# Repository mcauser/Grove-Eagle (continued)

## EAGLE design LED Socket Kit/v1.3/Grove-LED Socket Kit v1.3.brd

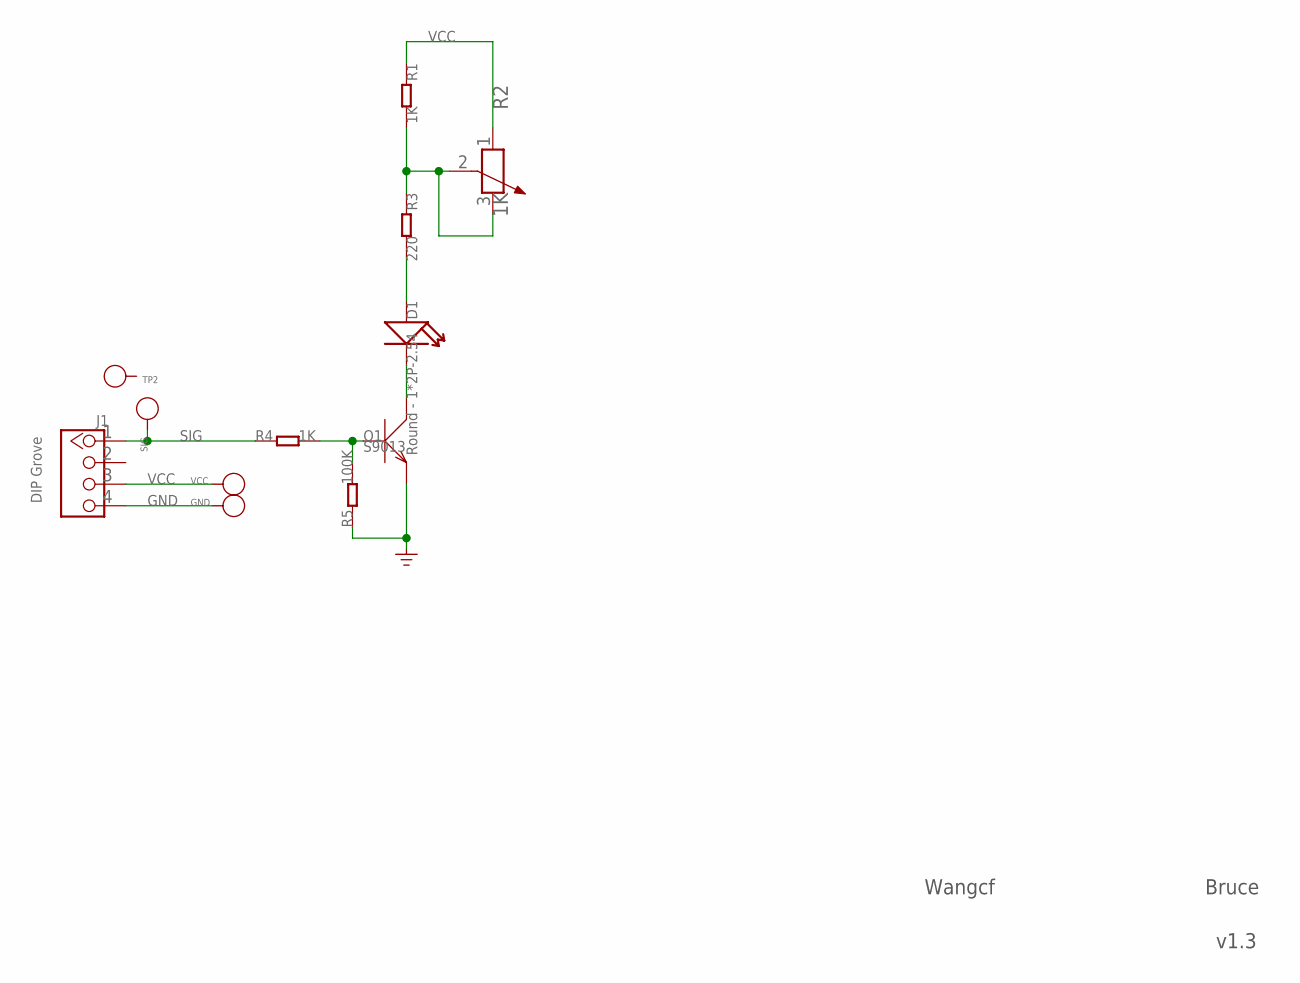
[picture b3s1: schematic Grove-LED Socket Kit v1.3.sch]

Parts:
D1: Round - 1*2P-2.54; LED-2P-2.54-6MM
GND: PAD-TEST-POINT'4545'; TP_4545
J1: DIP Grove; 2.0_1X4
Q1: S9013; SOT23
R1, R4: 1K; 0603
R2: 1K; 3P-SQUA-6.7X6.4
R3: 220; 0603
R5: 100K; 0603
SIG: PAD-TEST-POINT'4545'; TP_4545
TP2: PAD-TEST-POINT'4545'; TP_4545
VCC: PAD-TEST-POINT'4545'; TP_4545

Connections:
GND: GND.T, J1.4, Q1.2 (E), R5.1
unnamed: R1.2, R2.2 (3), R2.3 (2), R3.1
unnamed: D1.-, Q1.3 (C)
unnamed: D1.+, R3.2
unnamed: Q1.1 (B), R4.2, R5.2
SIG: J1.1, R4.1, SIG.T
VCC: J1.3, R1.1, R2.1, VCC.T

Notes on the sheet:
Wangcf
v1.3
Bruce

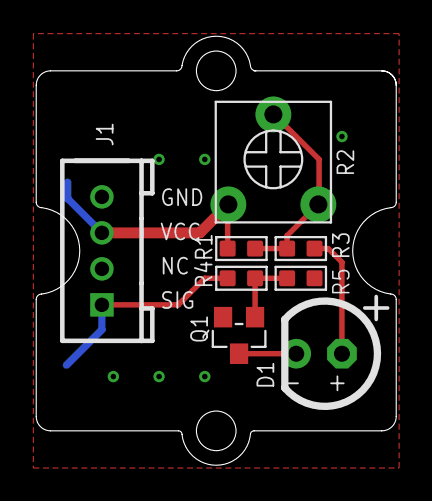
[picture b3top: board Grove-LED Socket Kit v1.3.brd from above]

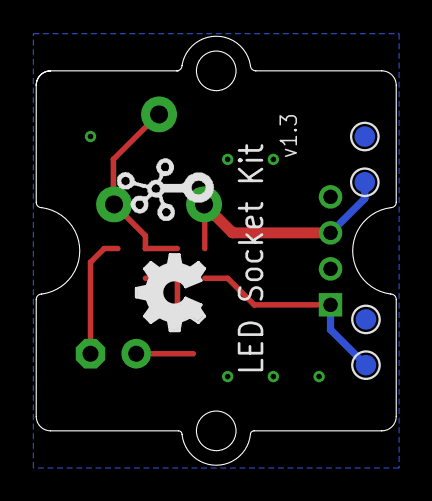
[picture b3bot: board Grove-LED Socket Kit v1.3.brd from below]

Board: 2 copper layers, 20.0 x 23.8 mm, 15 parts (6 on the bottom side), 7 nets.

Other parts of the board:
U$2: 1U-DIM-W/-DRILL
U$5: TWIGLOGO_SMALL
U$6: OSHW_FILLX150_NOTEXT

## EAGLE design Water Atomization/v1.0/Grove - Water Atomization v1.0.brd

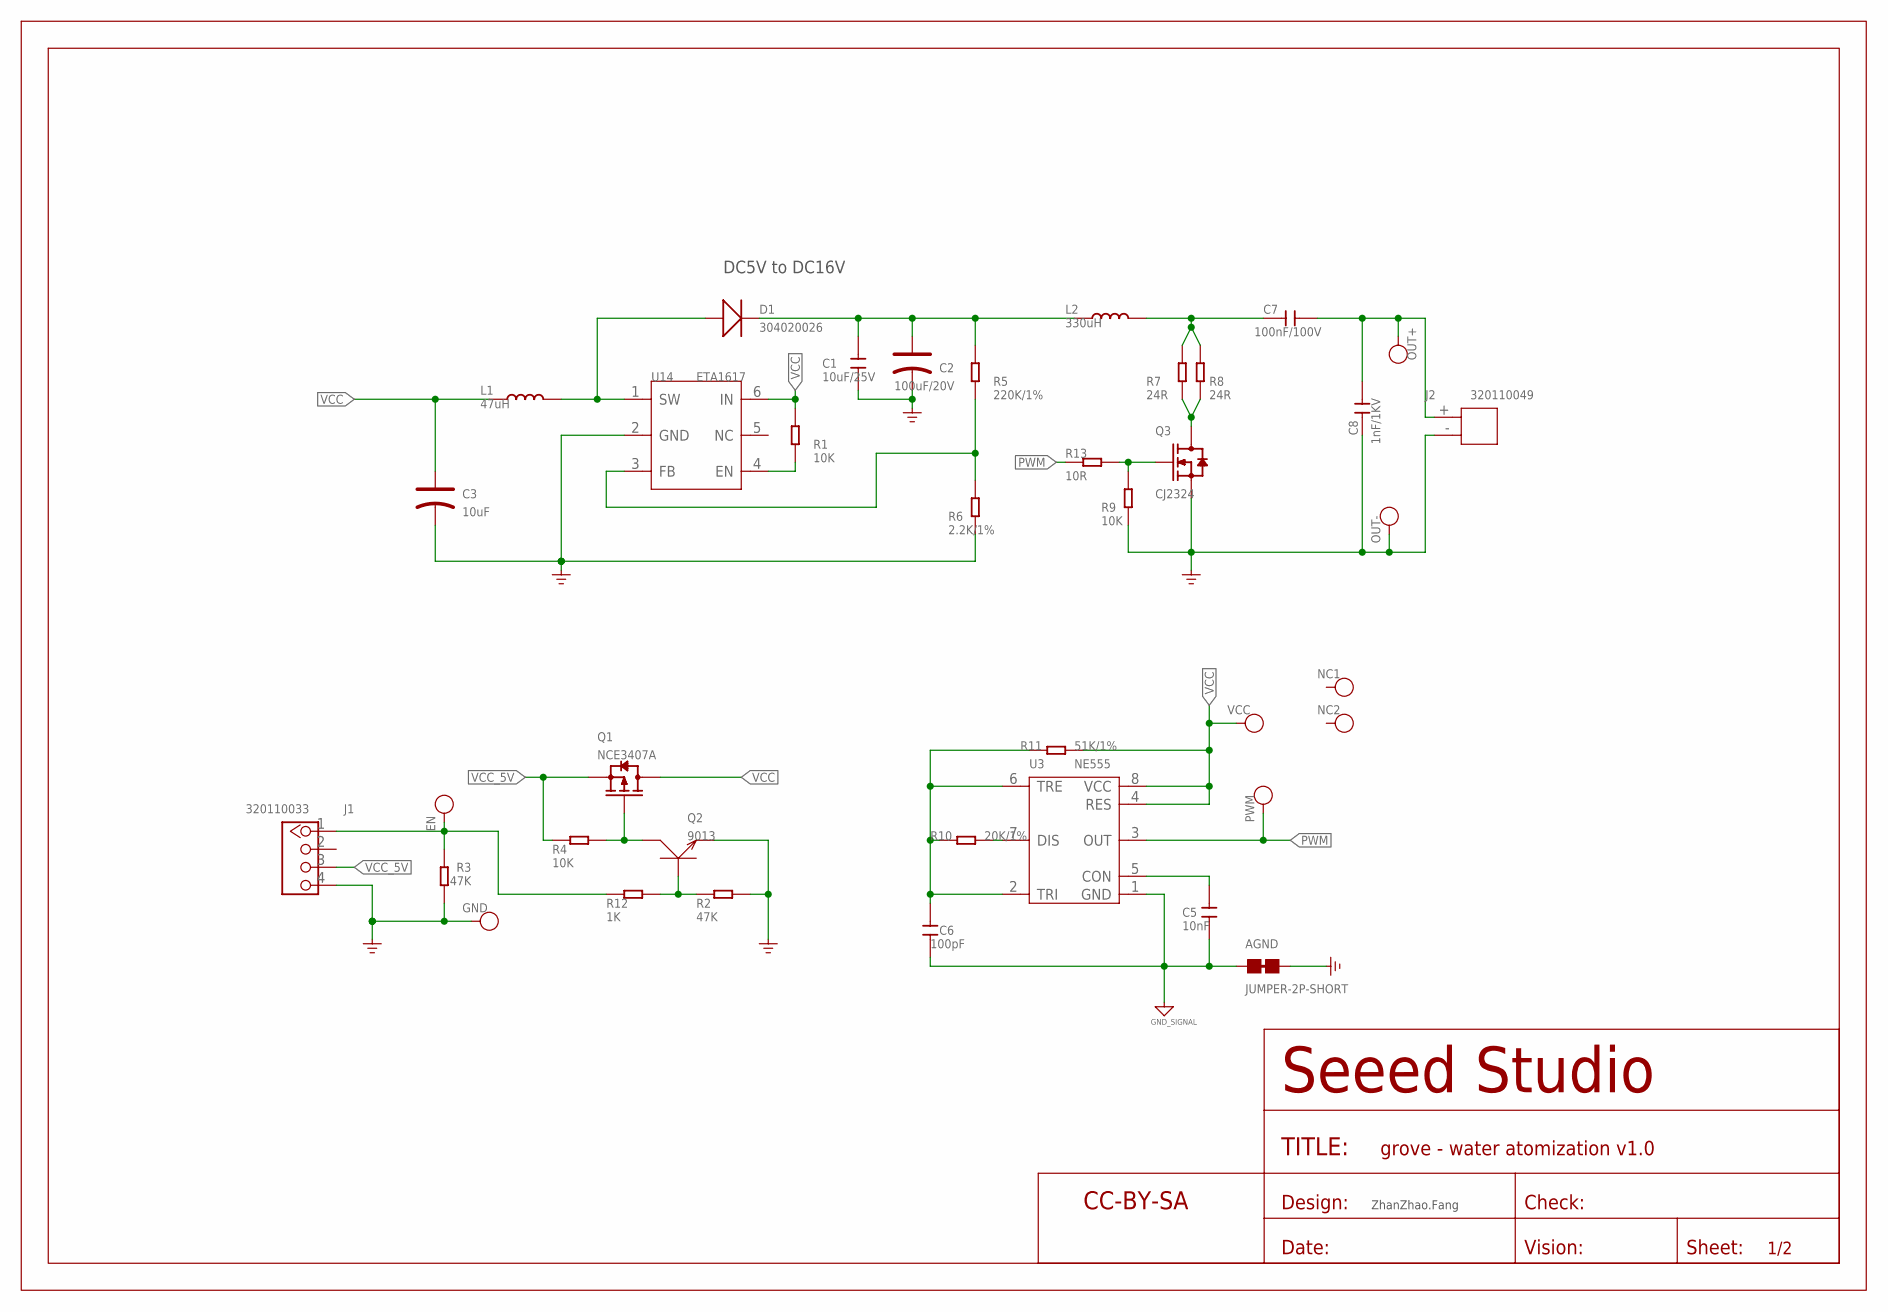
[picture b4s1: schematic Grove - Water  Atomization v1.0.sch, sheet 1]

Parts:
AGND: JUMPER-2P-SHORT; 2P-SMD-SHORT
C1: 10uF/25V; C1206
C2: 100uF/20V; AVX-D
C3: 10uF; AVX-B
C5: 10nF; C0402
C6: 100pF; C0402
C7: 100nF/100V; C0805
C8: 1nF/1KV; C1206
D1: 304020026; SOD-323
EN: DNP; TP-D45MIL
GND: DNP; TP-D45MIL
J1: 320110033; HW4-2.0
J2: 320110049; H2-2.0-6X4.5MM
L1: 47uH; INT2-SMD-4.8X4.8X3MM
L2: 330uH; INT2-SMD-4.8X4.8X3MM
NC1, NC2: DNP; TP-D45MIL
OUT+: DNP; TP-D45MIL
OUT-: DNP; TP-D45MIL
PWM: DNP; TP-D45MIL
Q1: NCE3407A; SOT-23
Q2: 9013; SOT-323
Q3: CJ2324; SOT-23
R1, R4, R9: 10K; R0402
R2, R3: 47K; R0402
R5: 220K/1%; R0402
R6: 2.2K/1%; R0402
R7, R8: 24R; R0805
R10: 20K/1%; R0402
R11: 51K/1%; R0402
R12: 1K; R0402
R13: 10R; R0402
U3: NE555; SOIC8-1.27-5X4MM
U14: ETA1617; SOT-23-6
U$1: DNP; SEEEDSTUDIO-PCB-FRAME
VCC: DNP; TP-D45MIL

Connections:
EN: EN.T, J1.1, R3.1, R12.2
FB: R5.1, R6.2, U14.3 (FB)
GND: AGND.2, C1.2, C2.-, C3.-, C8.2, GND.T, J1.4, J2.-, OUT-.T, Q2.2 (E), Q3.2 (S), R2.1, R3.2, R6.1, R9.1, U14.2 (GND)
unnamed: Q3.3 (D), R7.1, R8.1
unnamed: D1.+, L1.2, U14.1 (SW)
unnamed: R1.1, U14.4 (EN)
unnamed: C1.1, C2.+, D1.-, L2.1, R5.2
unnamed: Q1.1 (G), Q2.3 (C), R4.1
unnamed: Q2.1 (B), R2.2, R12.1
unnamed: C5.2, U3.5 (CON)
unnamed: Q3.1 (G), R9.2, R13.1
unnamed: C7.2, L2.2, R7.2, R8.2
unnamed: C7.1, C8.1, J2.+, OUT+.T
unnamed: R10.1, U3.7 (DIS)
unnamed: C6.2, R10.2, R11.1, U3.2 (TRI), U3.6 (TRE)
PWM: PWM.T, R13.2, U3.3 (OUT)
VCC: C3.+, L1.1, Q1.3 (D), R1.2, R11.2, U3.4 (RES), U3.8 (VCC), U14.6 (IN), VCC.T
VCC_5V: J1.3, Q1.2 (S), R4.2
\GND: AGND.1, C5.1, C6.1, U3.1 (GND)

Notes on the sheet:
DC5V to DC16V
ZhanZhao.Fang

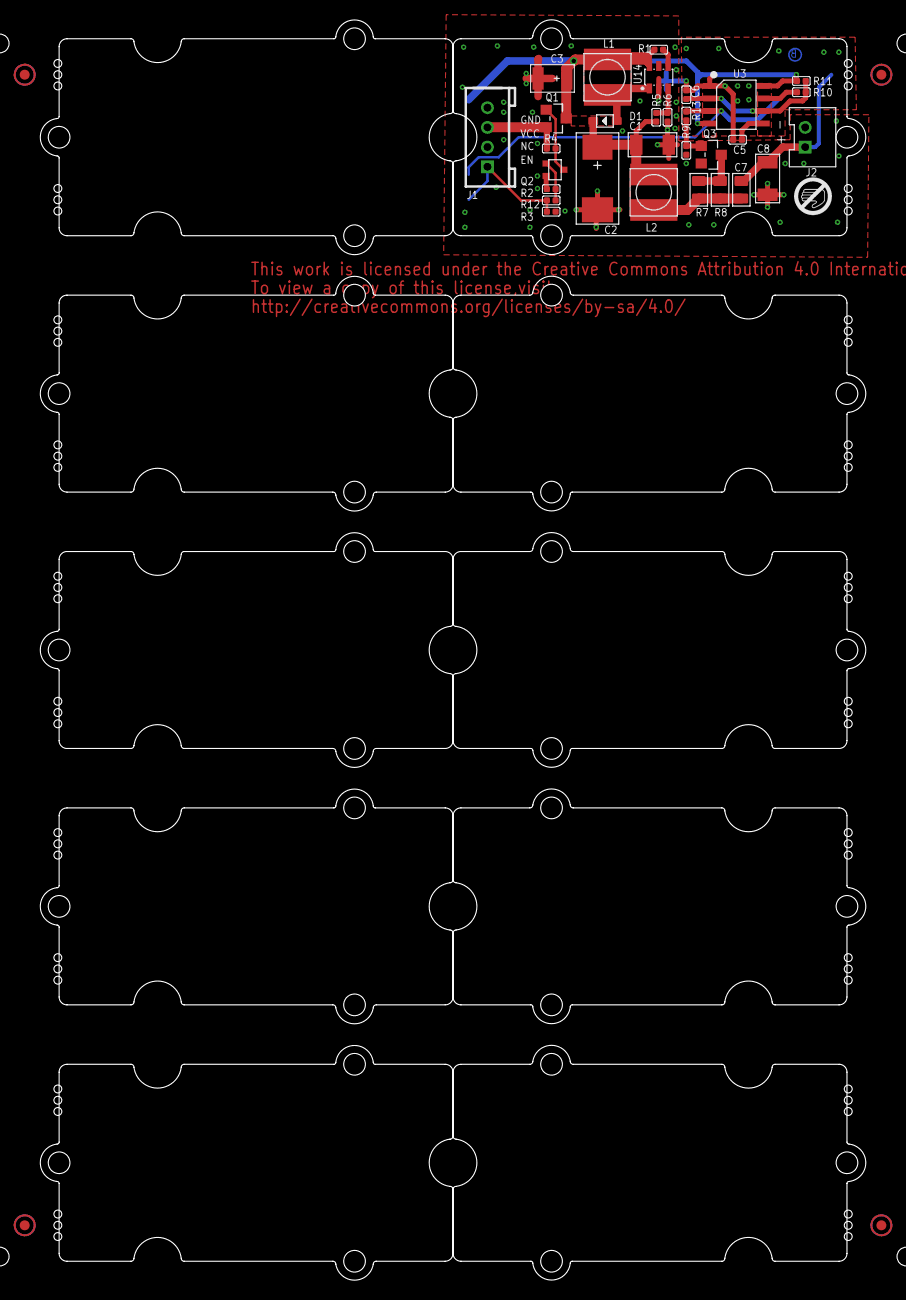
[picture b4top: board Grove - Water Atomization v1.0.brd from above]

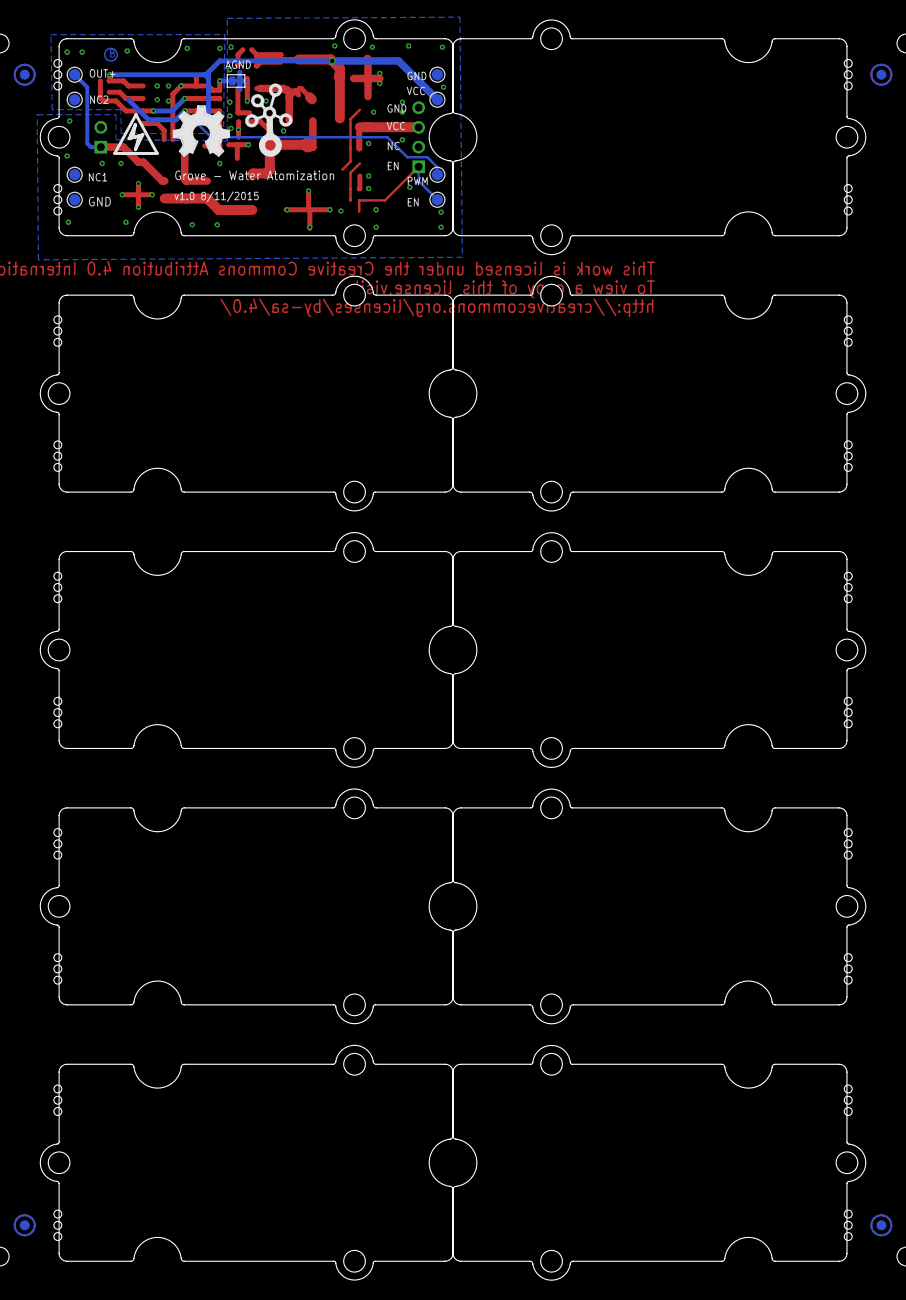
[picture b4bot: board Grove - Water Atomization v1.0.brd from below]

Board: 2 copper layers, 83.8 x 128.0 mm, 60 parts (15 on the bottom side), 19 nets.

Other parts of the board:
P1, P2, P3, P4, P5, P6, P7, P8: ROUND-MARK-1.0
U4, U5, U6, U7, U8, U9, U10, U11, U12, U13: GROVE-TEST-PLATFORM
U$5: OSHW_FILLX200_NOTEXT
U$7: GROVE-SILK-BIG

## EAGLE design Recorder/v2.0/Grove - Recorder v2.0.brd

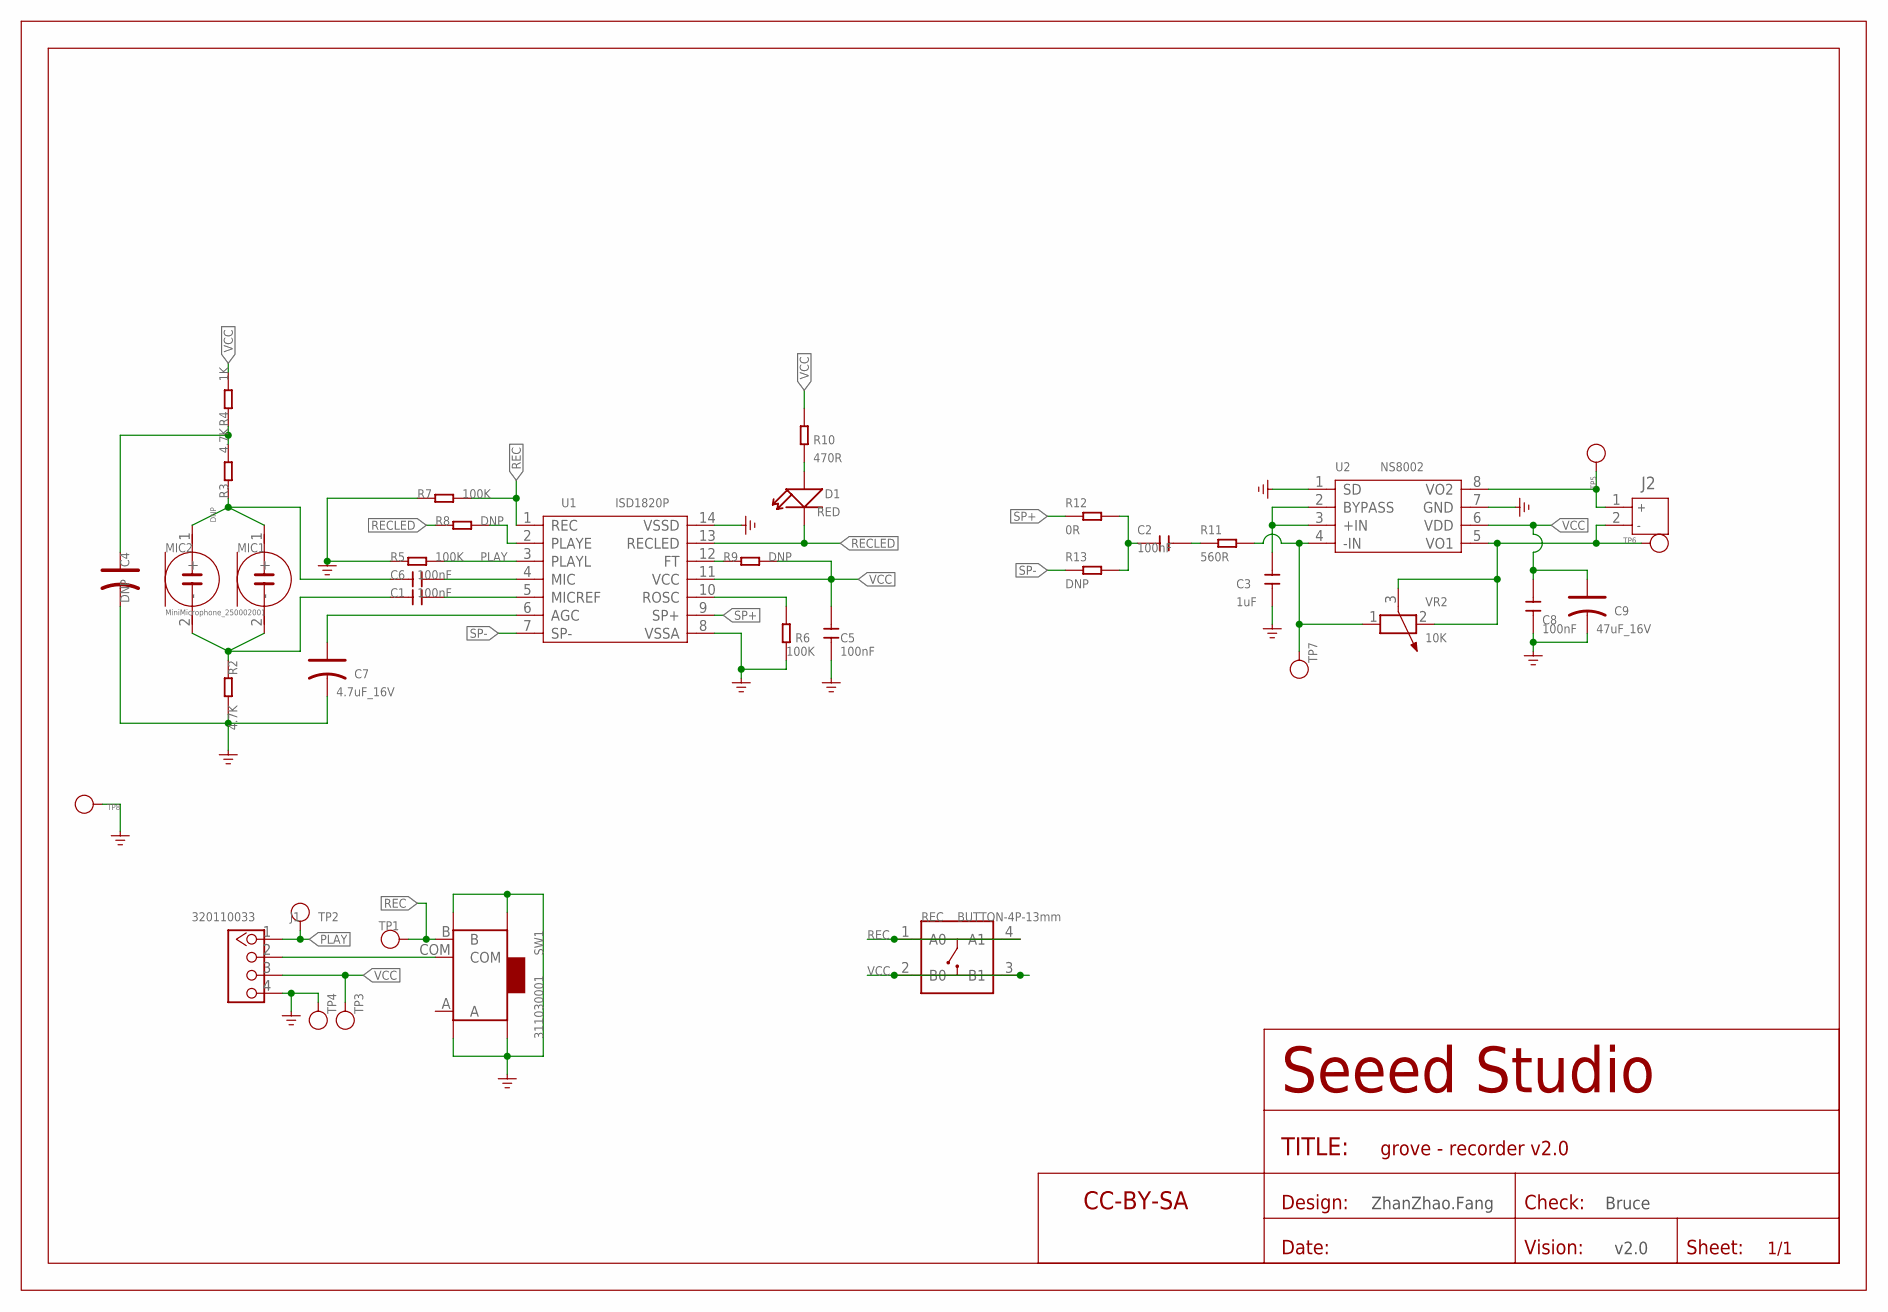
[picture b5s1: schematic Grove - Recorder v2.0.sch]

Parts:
C1, C5, C6, C8: 100nF; C0402
C2: 100nF; C0603
C3: 1uF; C0402
C4: DNP; AVX-A
C7: 4.7uF_16V; AVX-A
C9: 47uF_16V; AVX-B
D1: RED; LED-SIDE-VIEW-0603-RIGHT
FR1: SEEEDSTUDIO-OPEN-SCH-FRAME; SEEEDSTUDIO-PCB-FRAME
J1: 320110033; HW4-2.0
J2: 2P-2.0; JST-2.0
MIC1: MiniMicrophone_250002001; 2P-D8.9MM
MIC2: DNP; 2P-D8.9MM
R2, R3: 4.7K; R0402
R4: 1K; R0402
R5, R6, R7: 100K; R0402
R8, R9, R13: DNP; R0402
R10: 470R; R0402
R11: 560R; R0402
R12: 0R; R0402
REC: BUTTON-4P-13mm; 4P-6.0X6.0X5.0H
SW1: 311030001; SW7-SMD-L6.7X2.7X3.2MM
TP1, TP2, TP3, TP4, TP7: DNP; TP-D45MIL
TP5, TP6, TP8: DNP; TP_4545
U1: ISD1820P; DIP14
U2: NS8002; SOIC8-1.27-5X4MM
VR2: 10K; ADJR3-7.0X7.0X5.0MM

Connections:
GND: C3.1, C4.-, C5.2, C7.- (2), C8.1, C9.- (2), J1.4, R2.2, R5.1, R6.1, R7.1, SW1.SS1, SW1.SS2, SW1.SS3, SW1.SS4, TP4.T, TP8.T, U1.8 (VSSA), U1.14 (VSSD), U2.1 (SD), U2.7 (GND)
unnamed: R8.2, U1.2 (PLAYE)
unnamed: D1.1 (+), R10.1
unnamed: J2.1, TP5.T, U2.8 (VO2)
unnamed: J2.2, TP6.T, U2.5 (VO1), VR2.2, VR2.3
unnamed: C7.+ (1), U1.6 (AGC)
unnamed: C1.2, U1.5 (MICREF)
unnamed: C6.2, U1.4 (MIC)
unnamed: C3.2, U2.2 (BYPASS), U2.3 (+IN)
unnamed: C2.1, R11.1
unnamed: R11.2, TP7.T, U2.4 (-IN), VR2.1
unnamed: R9.1, U1.12 (FT)
unnamed: C2.2, R12.1, R13.1
unnamed: R6.2, U1.10 (ROSC)
unnamed: C4.+, R3.2, R4.1
unnamed: J1.2, SW1.COM
unnamed: C6.1, MIC1.1 (+), MIC2.1 (+), R3.1
unnamed: C1.1, MIC1.2 (-), MIC2.2 (-), R2.1
PLAY: J1.1, R5.2, TP2.T, U1.3 (PLAYL)
REC: R7.2, REC.1 (A0), REC.4 (A1), SW1.B, TP1.T, U1.1 (REC)
RECLED: D1.2 (-), R8.1, U1.13 (RECLED)
SP+: R12.2, U1.9 (SP+)
SP-: R13.2, U1.7 (SP-)
VCC: C5.1, C8.2, C9.+ (1), J1.3, R4.2, R9.2, R10.2, REC.2 (B0), REC.3 (B1), TP3.T, U1.11 (VCC), U2.6 (VDD)

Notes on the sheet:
ZhanZhao.Fang
Bruce
v2.0

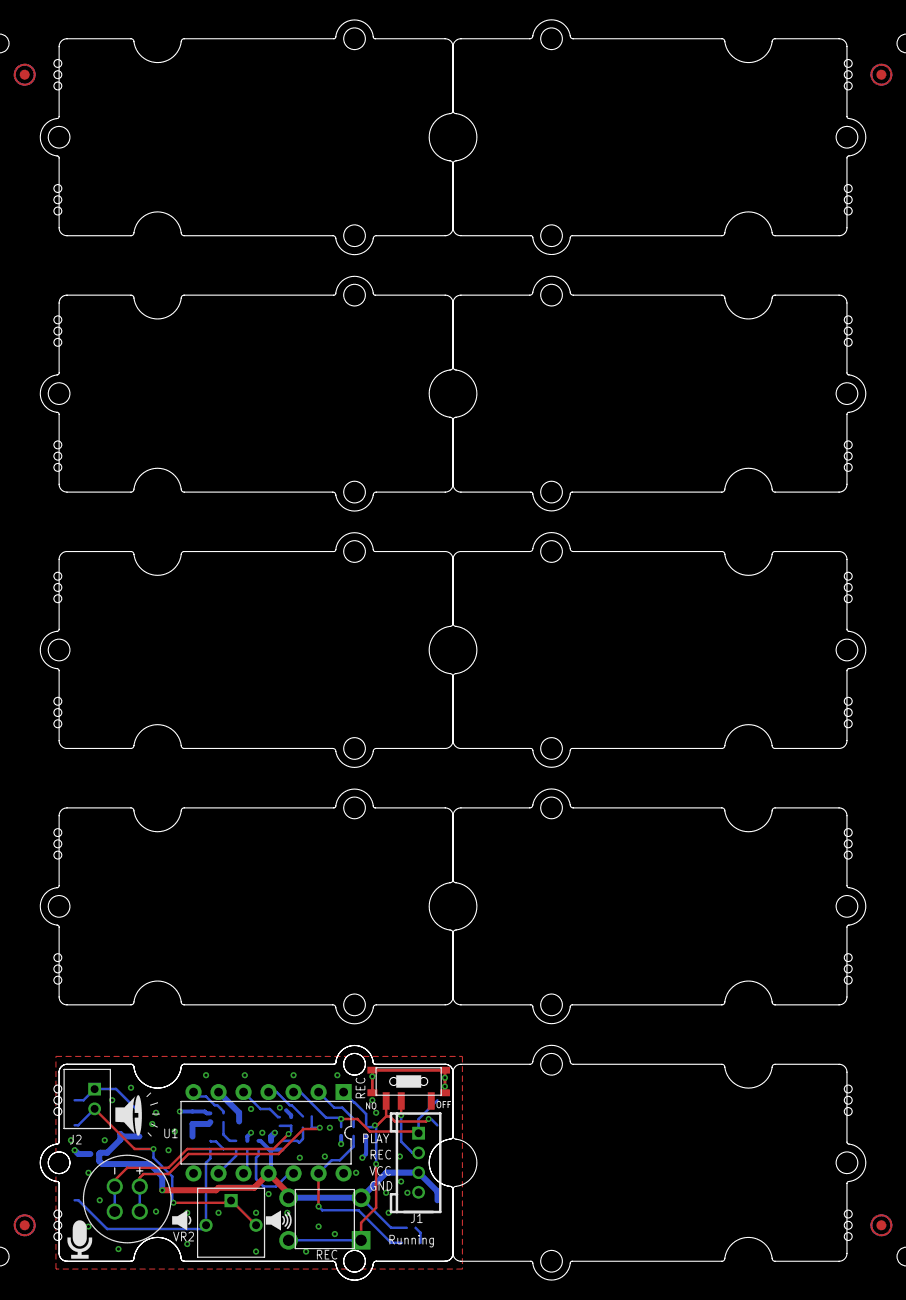
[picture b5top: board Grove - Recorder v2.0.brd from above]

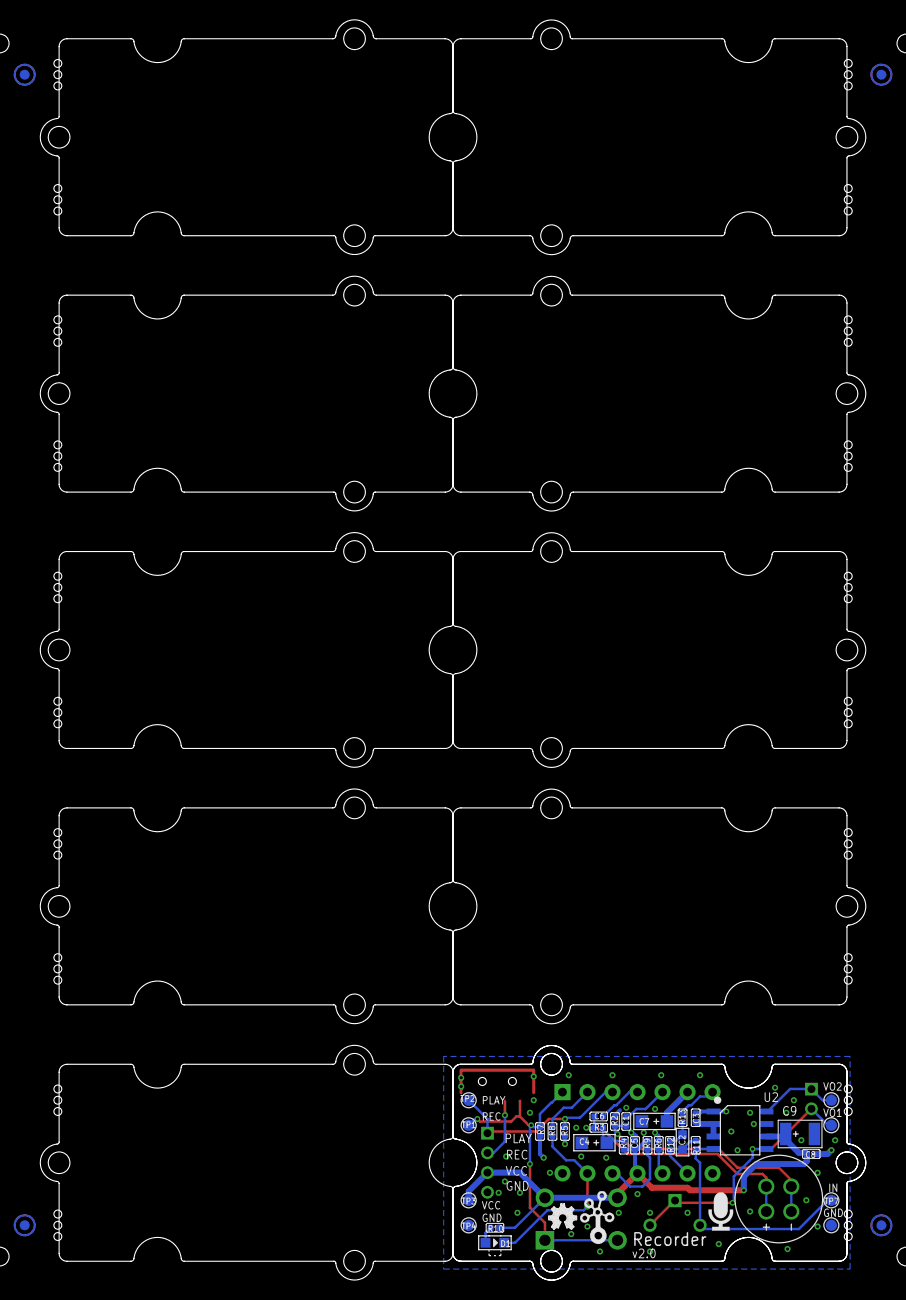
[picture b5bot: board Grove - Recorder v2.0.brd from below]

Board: 2 copper layers, 83.8 x 128.0 mm, 61 parts (38 on the bottom side), 24 nets.

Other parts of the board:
P1, P2, P3, P4, P5, P6, P7, P8: ROUND-MARK-1.0
U3, U4, U5, U6, U7, U8, U9, U10, U11, U12: GROVE-TEST-PLATFORM
U$9: GROVE-2CONNECTOR
U$10: TWIGLOGO_SMALL
U$11: OSHW_FILLX100_NOTEXT

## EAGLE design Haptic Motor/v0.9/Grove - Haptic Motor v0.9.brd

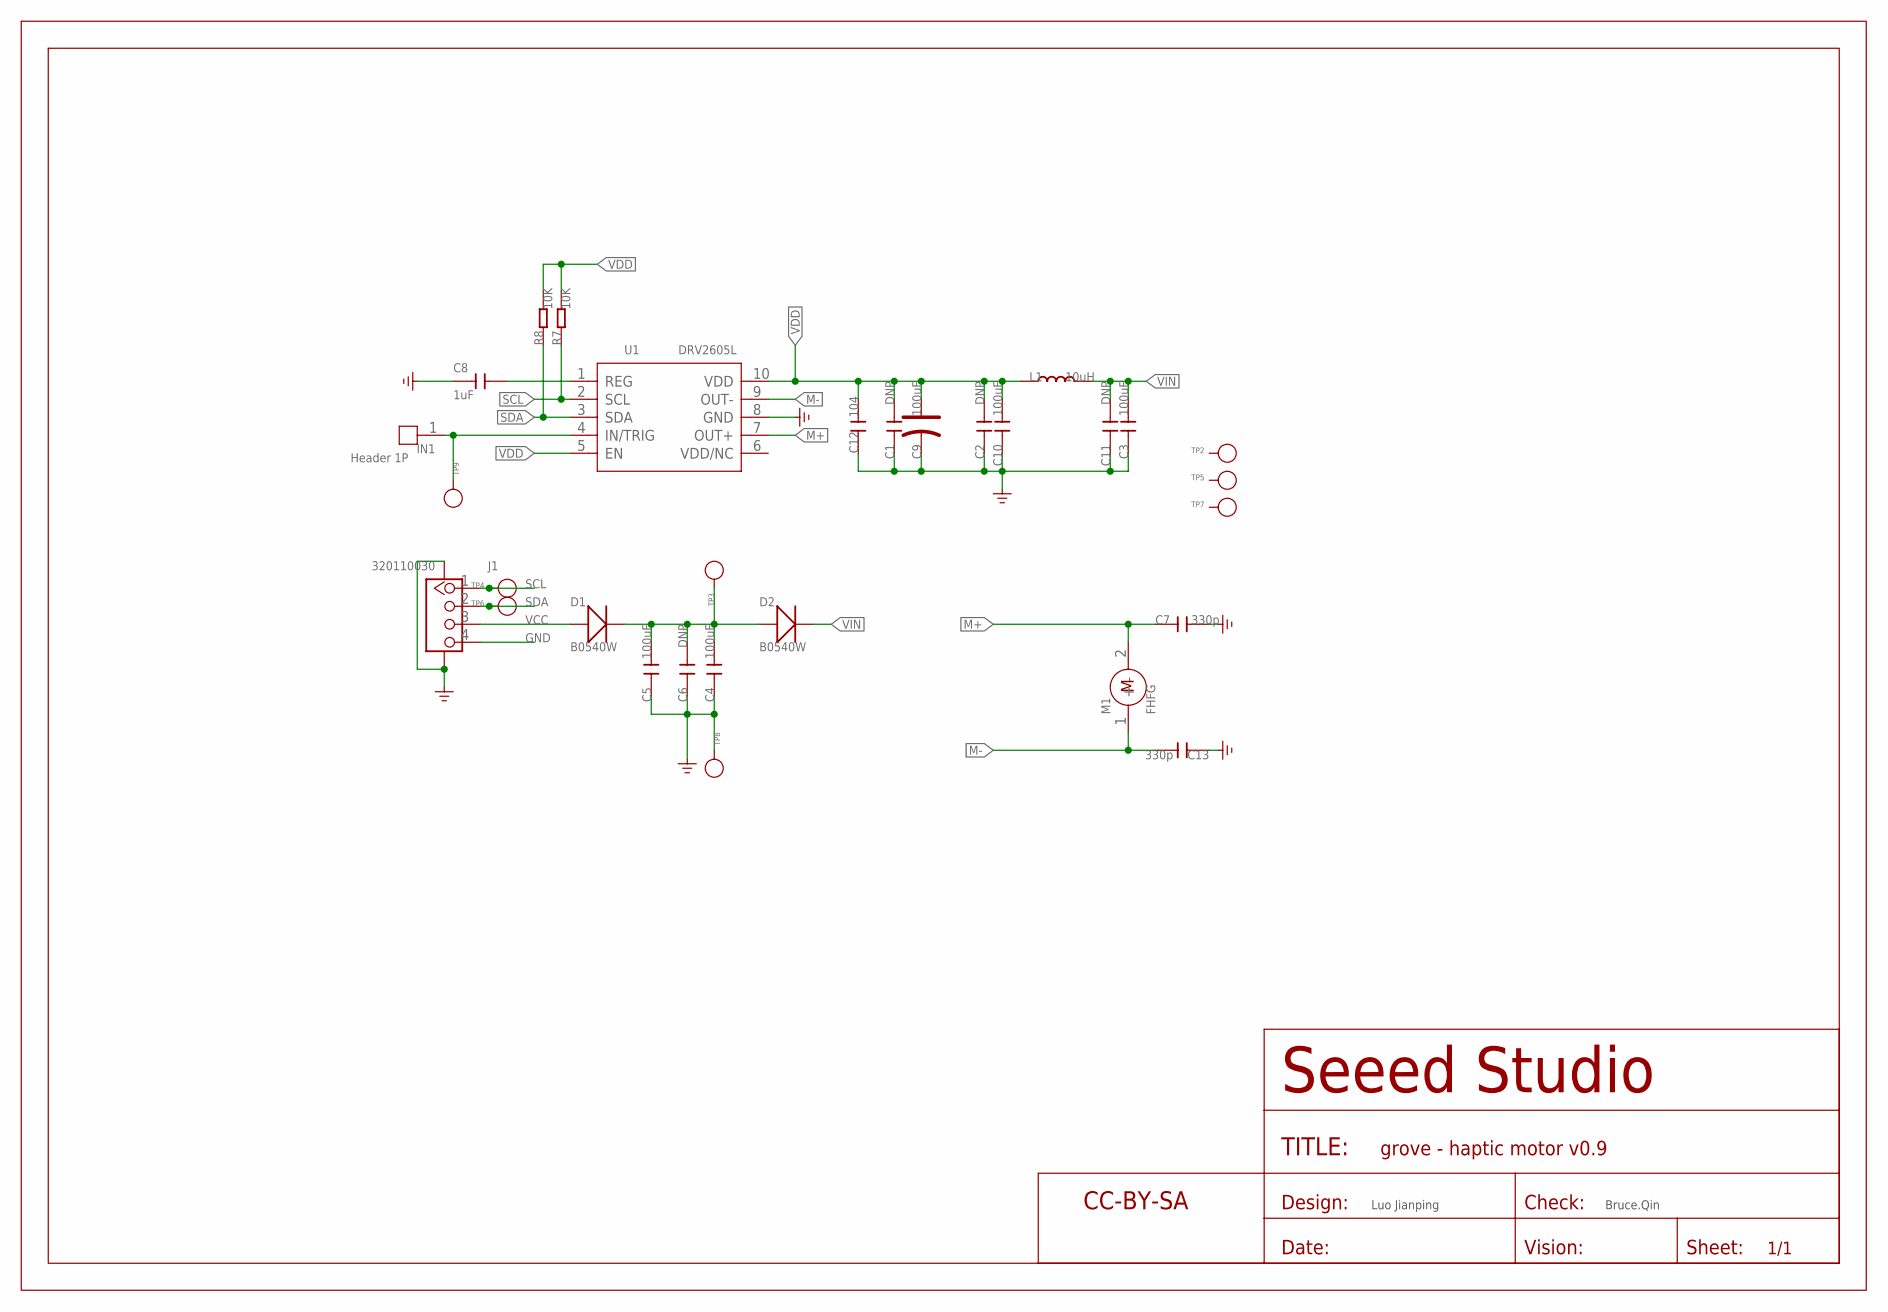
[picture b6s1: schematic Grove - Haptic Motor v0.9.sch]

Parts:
C1, C2, C6, C11: DNP; C0805
C3, C4, C10: 100uF; C1206
C5: 100uF; C0603
C7, C13: 330p; C0603
C8: 1uF; C0603
C9: 100uF; AVX-B
C12: 104; C0603
D1, D2: B0540W; SOD-123
IN1: Header 1P; 1P-65/35MIL
J1: 320110030; HW4-SMD-2.0
L1: 10uH; L0806
M1: FHFG; MTR2-SMD-D11.2MM
R7, R8: 10K; R0603
TP2, TP3, TP4, TP5, TP6, TP7, TP8, TP9: PAD-TEST-POINT'4545'; TP_4545
U1: DRV2605L; VSSOP10-0.5-3X3MM
U$9: SEEEDSTUDIO-OPEN-SCH-FRAME; SEEEDSTUDIO-PCB-FRAME

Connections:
GND: C1.2, C2.2, C3.2, C4.2, C5.2, C6.2, C7.2, C8.1, C9.-, C10.2, C11.2, C12.1, C13.1, J1.4, J1.SS1, J1.SS2, TP8.T, U1.8 (GND)
IN/TRIG2: IN1.1, TP9.T, U1.4 (IN/TRIG)
M+: C7.1, M1.2 (-), U1.7 (OUT+)
M-: C13.2, M1.1 (+), U1.9 (OUT-)
REG: C8.2, U1.1 (REG)
SCL: J1.1, R7.1, TP4.T, U1.2 (SCL)
SDA: J1.2, R8.1, TP6.T, U1.3 (SDA)
VCC: D1.+, J1.3
VDD: C1.1, C2.1, C9.+, C10.1, C12.2, L1.1, R7.2, R8.2, U1.5 (EN), U1.10 (VDD)
VIN: C3.1, C11.1, D2.-, L1.2
VIN-1: C4.1, C5.1, C6.1, D1.-, D2.+, TP3.T

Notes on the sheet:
Luo Jianping
Bruce.Qin

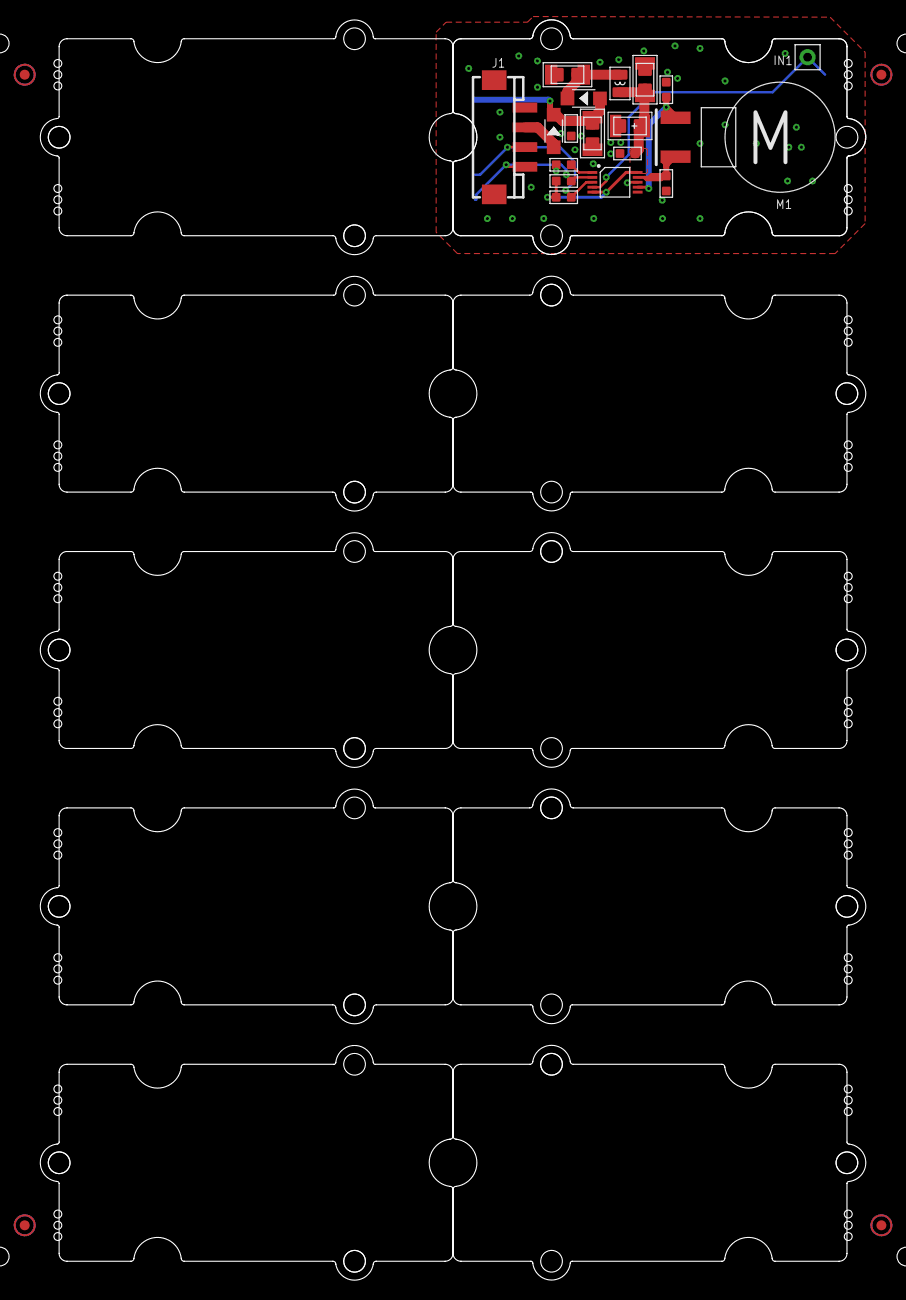
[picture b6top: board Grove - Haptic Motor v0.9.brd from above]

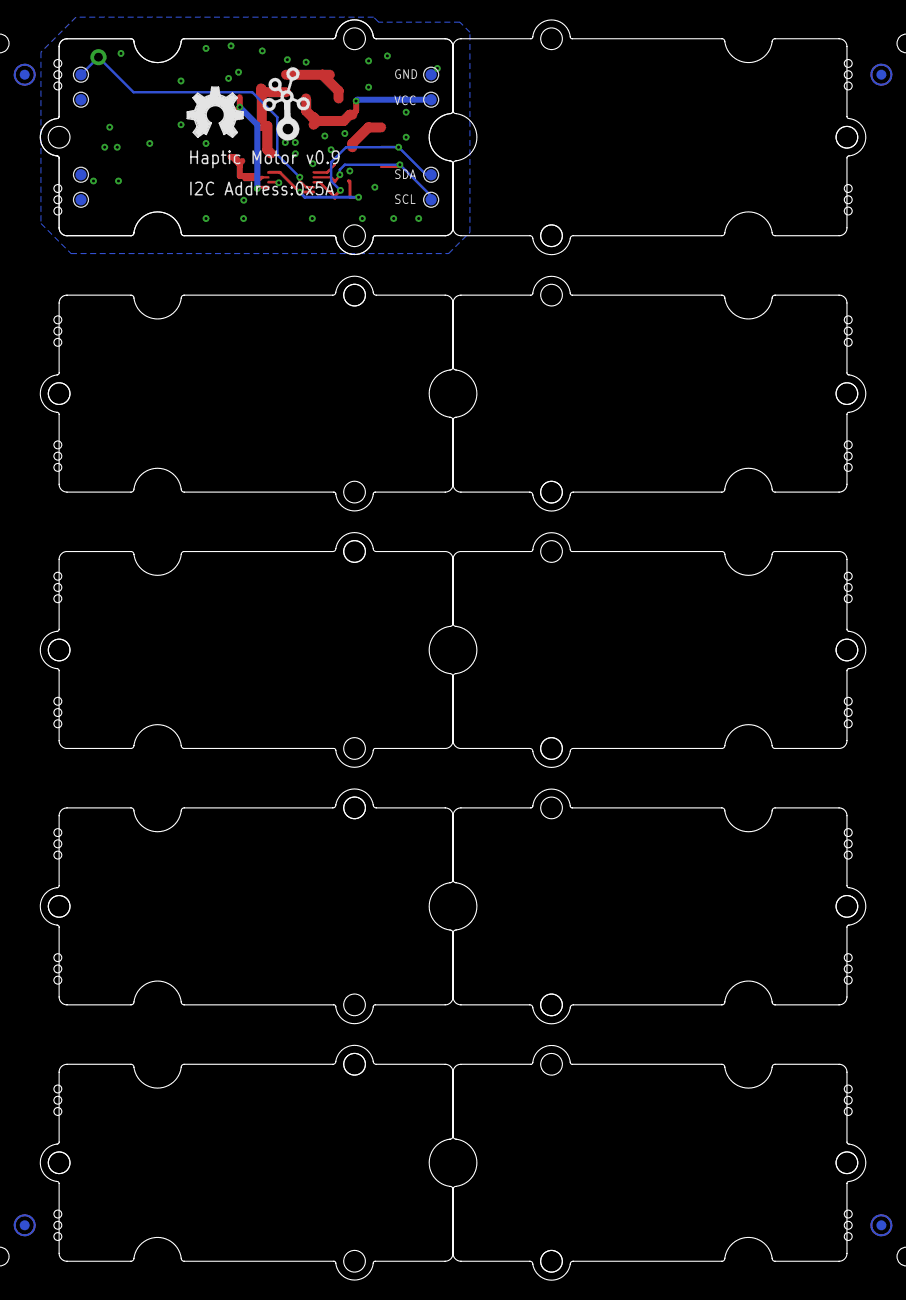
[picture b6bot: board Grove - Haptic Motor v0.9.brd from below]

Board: 2 copper layers, 83.8 x 128.0 mm, 51 parts (14 on the bottom side), 11 nets.

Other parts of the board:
P1, P2, P3, P4, P5, P6, P7, P8: ROUND-MARK-1.0
U2, U3, U4, U5, U6, U7, U8, U10, U11: GROVE-TEST-PLATFORM
U$5: GROVE-1*2-DRILL-SILK
U$6: OSHW_FILLX200_NOTEXT
U$7: TWIGLOGO
